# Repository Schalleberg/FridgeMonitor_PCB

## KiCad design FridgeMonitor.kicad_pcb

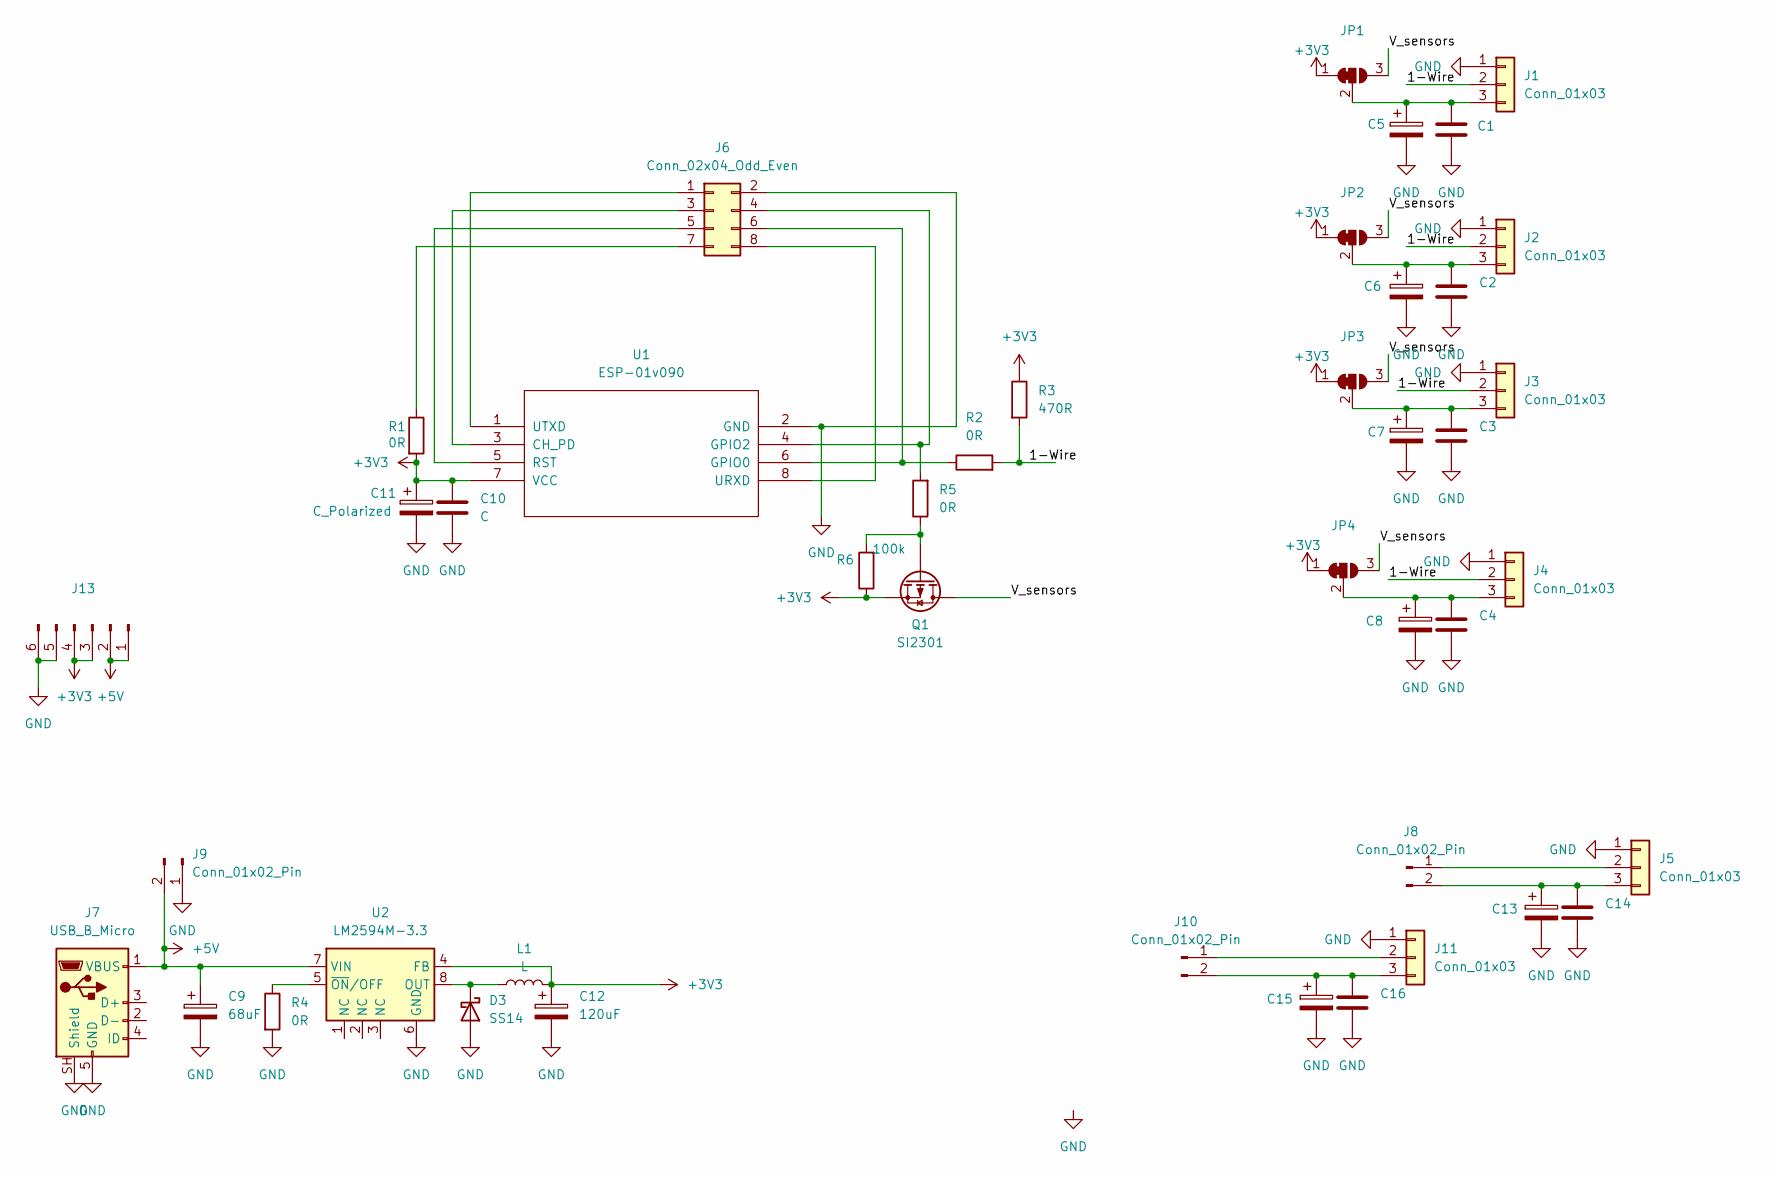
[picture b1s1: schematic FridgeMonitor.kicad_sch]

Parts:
C1, C2, C3, C4, C10, C14, C16: C; C_0805_2012Metric_Pad1.18x1.45mm_HandSolder
C5, C6, C7, C8, C11, C13, C15: C_Polarized; CP_Radial_D6.3mm_P2.50mm
C9: 68uF; CP_Radial_D6.3mm_P2.50mm
C12: 120uF; CP_Radial_D6.3mm_P2.50mm
D3: SS14; D_SMA
J1, J2, J3, J4, J5, J11: Conn_01x03; PhoenixContact_MC_1,5_3-G-5.08_1x03_P5.08mm_Horizontal
J6: Conn_02x04_Odd_Even; IDC-Header_2x04_P2.54mm_Vertical
J7: USB_B_Micro; USB_Micro-B_Molex-105017-0001
J8, J9, J10: Conn_01x02_Pin; PinSocket_1x02_P2.54mm_Vertical
J13: Conn_01x06_Pin; PinHeader_1x06_P2.54mm_Vertical
JP1, JP2, JP3, JP4: SolderJumper_3_Bridged12; SolderJumper-3_P1.3mm_Open_Pad1.0x1.5mm
L1: L; L_Radial_D12.5mm_P7.00mm_Fastron_09HCP
Q1: SI2301; TSOT-23
R1, R2, R4, R5: 0R; R_0805_2012Metric_Pad1.20x1.40mm_HandSolder
R3: 470R; R_0805_2012Metric_Pad1.20x1.40mm_HandSolder
R6: 100k; R_0805_2012Metric_Pad1.20x1.40mm_HandSolder
U1: ESP-01v090; ESP-01
U2: LM2594M-3.3; SOIC-8_3.9x4.9mm_P1.27mm

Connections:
+3V3: C10.1, C11.1, C12.1, J13.3, J13.4, JP1.1 (A), JP2.1 (A), JP3.1 (A), JP4.1 (A), L1.2, Q1.2 (S), R1.2, R3.1, R6.1, U1.7 (VCC), U2.4 (FB)
+5V: C9.1, J7.1 (VBUS), J9.2, J13.1, J13.2, U2.7 (VIN)
/1-Wire: J1.2, J2.2, J3.2, J4.2, R2.2, R3.2
/V_sensors: JP1.3 (B), JP2.3 (B), JP3.3 (B), JP4.3 (B), Q1.3 (D)
GND: C1.2, C2.2, C3.2, C4.2, C5.2, C6.2, C7.2, C8.2, C9.2, C10.2, C11.2, C12.2, C13.2, C14.2, C15.2, C16.2, D3.2 (A), J1.1, J2.1, J3.1, J4.1, J5.1, J6.2, J7.5 (GND), J7.SH (Shield), J9.1, J11.1, J13.5, J13.6, R4.2, U1.2 (GND), U2.6 (GND)
unnamed: D3.1 (K), L1.1, U2.8 (OUT)
unnamed: C1.1, C5.1, J1.3, JP1.2 (C)
unnamed: C2.1, C6.1, J2.3, JP2.2 (C)
unnamed: C3.1, C7.1, J3.3, JP3.2 (C)
unnamed: C4.1, C8.1, J4.3, JP4.2 (C)
unnamed: J5.2, J8.1
unnamed: C13.1, C14.1, J5.3, J8.2
unnamed: J6.1, U1.1 (UTXD)
unnamed: J6.3, U1.3 (CH_PD)
unnamed: J6.4, R5.2, U1.4 (GPIO2)
unnamed: J6.5, U1.5 (RST)
unnamed: J6.6, R2.1, U1.6 (GPIO0)
unnamed: J6.7, R1.1
unnamed: J6.8, U1.8 (URXD)
unnamed: J10.1, J11.2
unnamed: C15.1, C16.1, J10.2, J11.3
unnamed: Q1.1 (G), R5.1, R6.2
unnamed: R4.1, U2.5 (~ON/OFF)

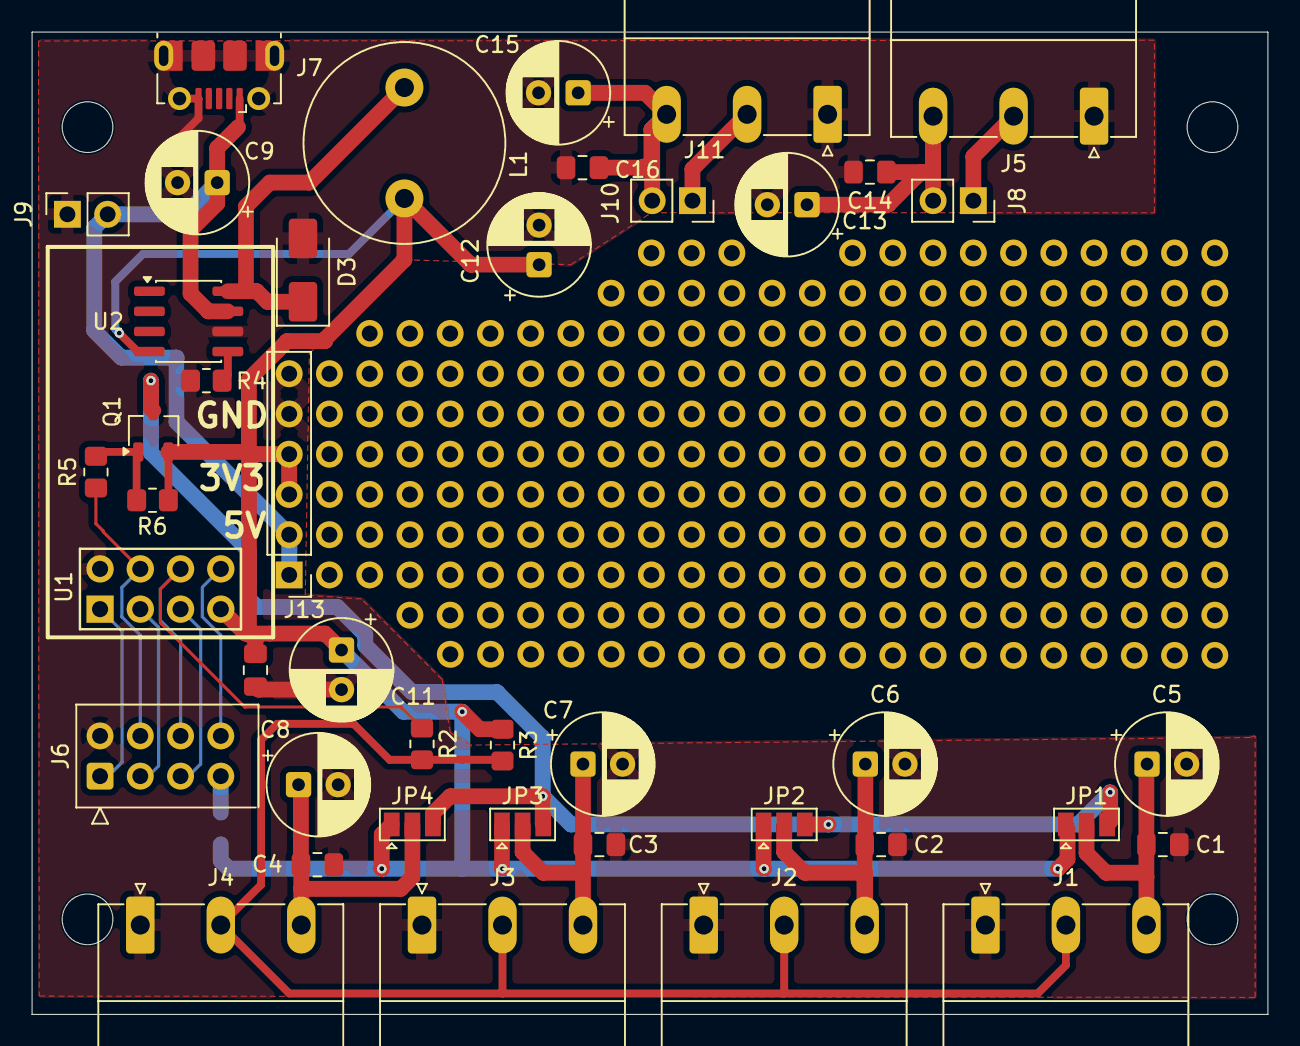
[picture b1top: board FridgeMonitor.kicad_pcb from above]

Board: 2 copper layers, 78.0 x 62.0 mm, 43 parts (1 on the bottom side), 23 nets.

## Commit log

2026-05-24 Datasheets case
2026-05-24 Backup
2026-05-24 For the moment all routed, except GND
2026-05-26 All routet except ground plane plus additional footprints
2026-05-28 all routed, except GND
2026-05-28 GND plane, DRC ok
2026-05-29 FIX: GND for ESP01 module
